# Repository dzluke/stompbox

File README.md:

# CNMAT stompbox 2.0
Read about the project here: https://cnmat.berkeley.edu/projects/stompbox-20-2019

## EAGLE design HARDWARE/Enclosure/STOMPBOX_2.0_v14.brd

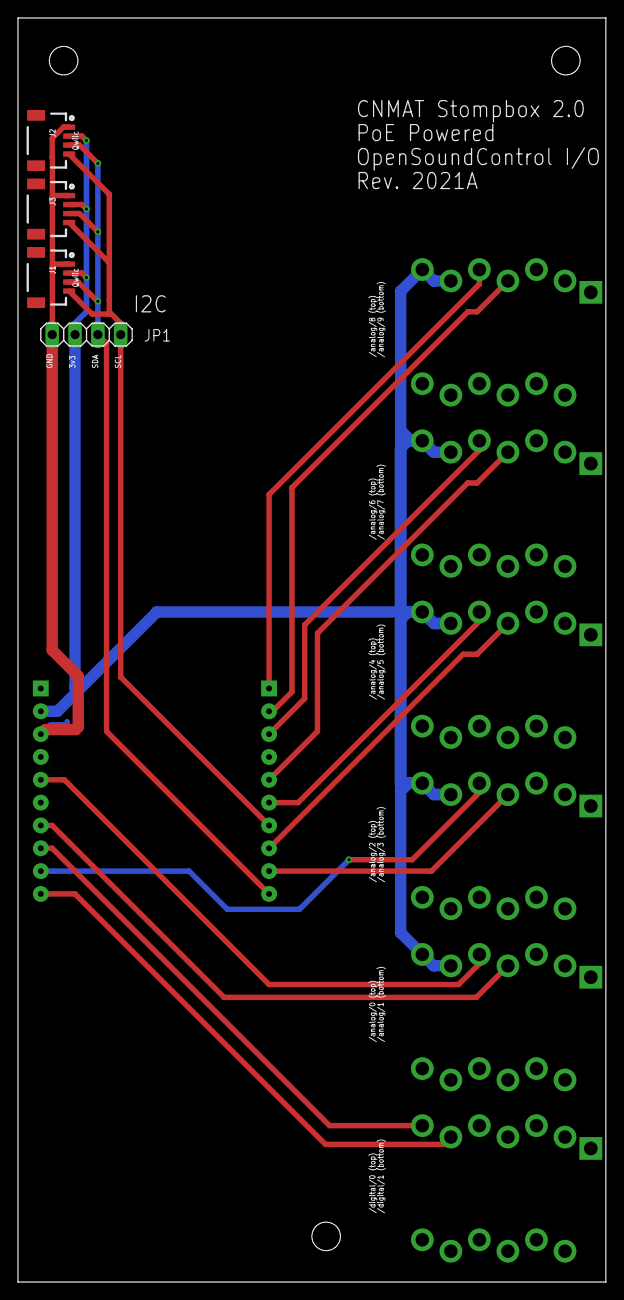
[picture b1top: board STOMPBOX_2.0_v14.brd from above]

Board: 2 copper layers, 65.4 x 140.6 mm, 11 parts (0 on the bottom side), 16 nets.

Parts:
J1, J2, J3: 1X04_1MM_RA
JP1: PINHD-1X4; 1X04
U$1, U$2, U$3, U$4, U$5, U$6: NSJ12HC
U$8: ESP32-POE-ISO

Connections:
+3.3V: J1.2, J2.2, J3.2, JP1.2, U$2.TB, U$2.TT, U$3.TB, U$3.TT, U$4.TB, U$4.TT, U$5.TB, U$5.TT, U$6.TB, U$6.TT, U$8.+3V3
GND: J1.1, J2.1, J3.1, JP1.1, U$1.GND, U$1.SB, U$1.ST, U$2.GND, U$2.SB, U$2.ST, U$3.GND, U$3.SB, U$3.ST, U$4.GND, U$4.SB, U$4.ST, U$5.GND, U$5.SB, U$5.ST, U$6.GND, U$6.SB, U$6.ST, U$8.GND
unnamed: U$1.TT, U$8.GPIO3
unnamed: U$1.TB, U$8.GPIO5
unnamed: U$2.RT, U$8.GPIO0
unnamed: U$2.RB, U$8.GPIO2
unnamed: U$3.RT, U$8.GPIO4
unnamed: U$3.RB, U$8.GPIO14
unnamed: U$4.RB, U$8.GPIO15
unnamed: U$4.RT, U$8.GPIO32
unnamed: U$5.RB, U$8.GPIO33
unnamed: U$6.RT, U$8.GPIO39
unnamed: U$6.RB, U$8.GPIO36
unnamed: U$5.RT, U$8.GPIO35
unnamed: J1.4, J2.4, J3.4, JP1.4, U$8.GPIO16
unnamed: J1.3, J2.3, J3.3, JP1.3, U$8.GPIO13

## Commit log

2019-10-22 Able to send UDP packets over wifi
2019-10-23 Send OSC bundle of random ints
2019-10-24 Programmatically create addrs; send analog
2019-11-11 Send input from one pin
2019-11-21 Receive OSC message from Max
2019-11-21 Calibrate digital pins
2019-11-27 Use calibration values to map analog input
2020-01-29 state of materials at end of fall 2019
2020-02-05 Display IP on startup; filter messages based on stompbox IP
2020-02-09 Display calibration countdown
2020-06-22 Patch works and add help file
2020-06-23 Rename to cnmat.o.stompbox2
2020-06-23 rm old name patch
2020-06-29 Stompbox will send only to user IP instead of broadcasting
2020-06-29 Edit helpfile
2020-08-11 Add example for esp32poe
2020-11-10 Add functionality for UDP with ESP32-POE-ISO
2020-12-14 Add method for displaying IP
2020-12-30 Fix calibration method
2020-12-30 Update max patch and helpfile to reflect PoE changes
2021-01-03 Max patch receives data, display works
2021-01-04 Add method for turning backlight on/off
2021-01-04 Add button and fix calibration
2021-01-04 Update helpfile
2021-02-23 Update to include Jeremy's code
2021-02-23 Jeremy fixes I2C conflict with distance sensor
2021-03-04 Adding folder HARDWARE
2021-03-05 Adding Fusion 360 file for enclosure
2021-03-09 Submitting Renderings of Enclosure
    Adding some renderings from Fusion360 showing prototype enclosure.
2021-03-10 Fixing Board Layout
    After getting prototype PCBs from JLCPCB today, we found the pin headers for the ESP32-POE-ISO part were undersized. Update addresses this.
2021-04-28 Add /getIP and /reportIP
2021-04-28 Modify max object to constantly send init msg
2021-04-28 Update helpfile to include new osc commands
2021-09-22 Remove distance sensor code
2021-09-23 Fix analogRead line in updateCalibration
2021-10-05 Update analog pin assignments to correctly map to addresses

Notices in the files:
parts and their libraries:
SparkFun-Connectors: Licensing: Creative Commons ShareAlike 4.0 International - https://creativecommons.org/licenses/by-sa/4.0
